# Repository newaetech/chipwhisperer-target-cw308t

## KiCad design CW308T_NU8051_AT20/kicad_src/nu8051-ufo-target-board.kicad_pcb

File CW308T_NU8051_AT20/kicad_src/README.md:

# N76e003 UFO Target board for the Chipwhisper UFO board

Tested and working, gerbers, BOM, and placement files are in `jlcpcb/`

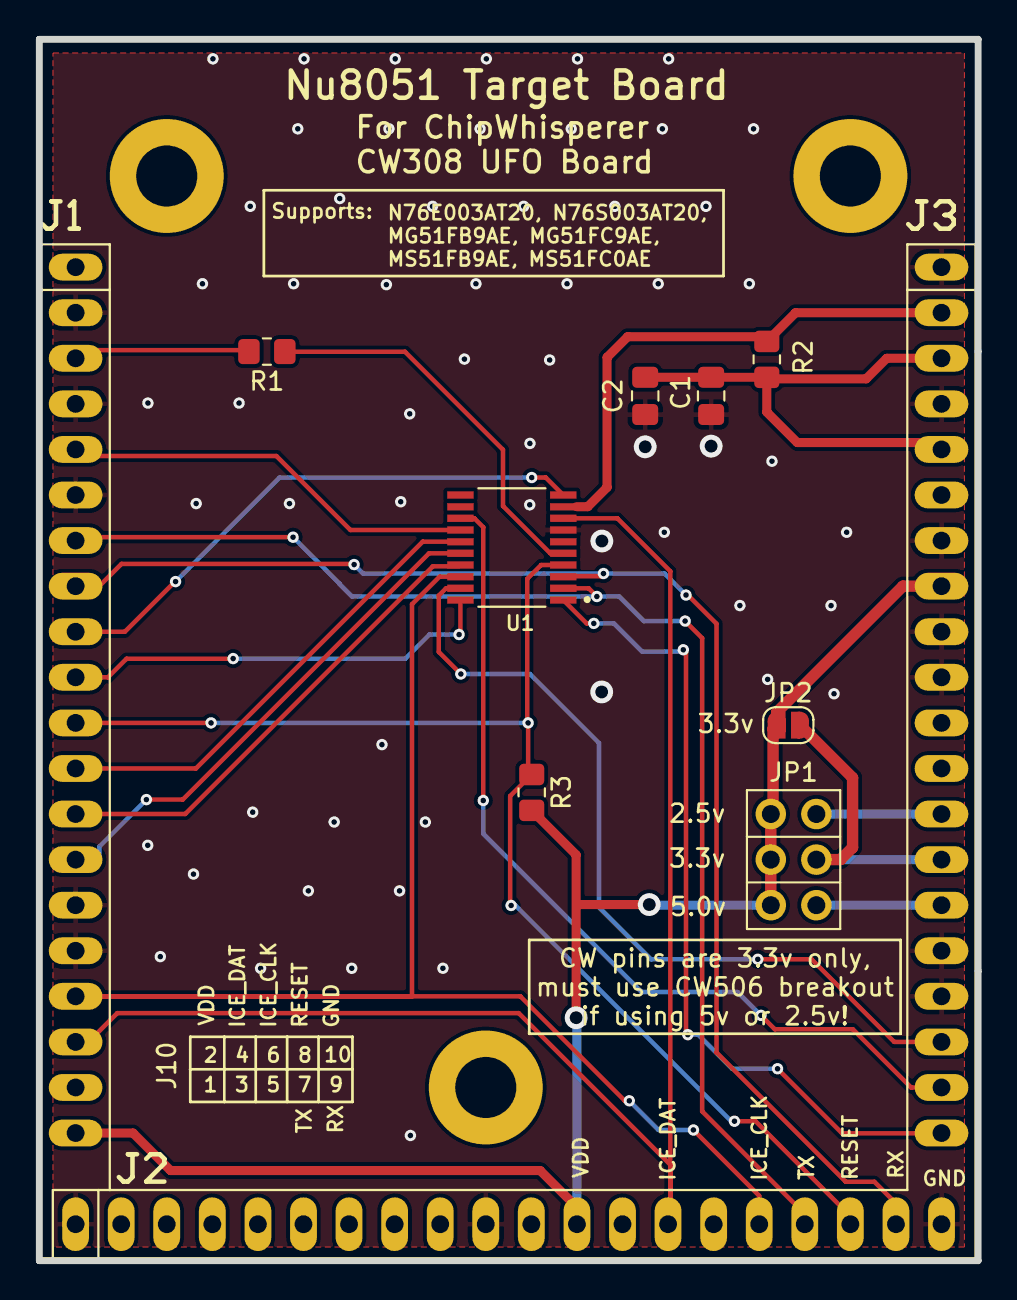
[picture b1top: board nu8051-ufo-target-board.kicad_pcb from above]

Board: 2 copper layers, 52.3 x 68.1 mm, 9 parts (0 on the bottom side), 23 nets.

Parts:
C1: 100nF; C_0805_2012Metric_Pad1.18x1.45mm_HandSolder
C2: 2.2uF (OPT); C_0805_2012Metric_Pad1.18x1.45mm_HandSolder
J1: CW308T_CONNBOARD
JP1: Jumper_2_Open; PinHeader_2x03_P2.54mm_Vertical
JP2: SolderJumper_2_Open; SolderJumper-2_P1.3mm_Open_RoundedPad1.0x1.5mm
R1: 100R; R_0805_2012Metric_Pad1.20x1.40mm_HandSolder
R2: 51R; R_0805_2012Metric_Pad1.20x1.40mm_HandSolder
R3: 10K; R_0805_2012Metric_Pad1.20x1.40mm_HandSolder
U1: N76E003AT20; SOP65P640X120-20N

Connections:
+2V5: J1.C13 (VCC2.5V), JP1.2 (B1)
+3.3V: J1.C14 (VCC3.3V), JP1.4 (B2), JP2.2 (B)
+5V: J1.C15 (VCC5.0V), JP1.6 (B3)
CLK: R1.1, U1.5 (P3.0/~INT0/OSCIN/AIN1)
CLKOUT: J1.A5 (CLKIN), U1.14 (P1.1/PWM1/IC1/AIN7/CLO)
GND: C1.2, C2.2, J1.A2 (GND), J1.A4 (GND), J1.A6 (GND), J1.A15 (GND), J1.A16 (GND), J1.B1 (GND), J1.B10 (GND), J1.B20 (HDR10), J1.C1 (GND), J1.C4 (GND), J1.C7 (GND), J1.C9 (GND), J1.C10 (GND), J1.C16 (GND), J1.C17 (GND), U1.7 (GND)
GPI01: J1.A7 (GPIO1), J1.B17 (HDR7), U1.2 (P0.6/TXD/AIN3)
GPI02: J1.A8 (GPIO2), J1.B19 (HDR9), U1.3 (P0.7/RXD/AIN2)
GPI03: J1.A9 (GPIO3), U1.10 (P1.5/PWM5/IC7/~SS)
GPI04: J1.A10 (GPIO4), U1.20 (P0.4/AIN5/STADC/PWM3/IC3)
LED1: J1.C18 (LED1), U1.19 (P0.3/PWM5/IC5/AIN6)
LED2: J1.C19 (LED2), U1.13 (P1.2/PWM0/IC0)
LED3: J1.C20 (LED3), U1.1 (P0.5/PWM2/IC6/T0/AIN4)
MISO: J1.A13 (MISO), U1.17 (P0.1/PWM4/IC4/MISO)
MOSI: J1.A14 (MOSI), U1.16 (P0.0/PWM3/IC3/MOSI/T1)
unnamed: J1.A3 (CLKOUT), R1.2
unnamed: C1.1, C2.1, J1.C3 (SHUNTH), J1.C5 (FILT_LP), R2.2
PDIC: J1.A17 (PDIC), J1.B16 (HDR6), U1.18 (P0.2/ICPCK/OCDCK/RXD_1/[SCL])
PDID: J1.A18 (PDID), J1.B14 (HDR4), U1.8 (P1.6/[SDA]/TXD_1/ICPDA/OCDDA)
RST: J1.A11 (NRST), J1.B18 (HDR8), R3.2, U1.4 (P2.0/~RST)
SCK: J1.A12 (SCK), U1.15 (P1.0/PWM2/IC2/SPCLK)
VBUS: J1.C2 (SHUNTL), R2.1, U1.9 (VDD)
VCC: J1.A20 (VREF), J1.B12 (HDR2), J1.C8 (FILTIN), JP1.1 (A1), JP1.3 (A2), JP1.5 (A3), JP2.1 (A), R3.1

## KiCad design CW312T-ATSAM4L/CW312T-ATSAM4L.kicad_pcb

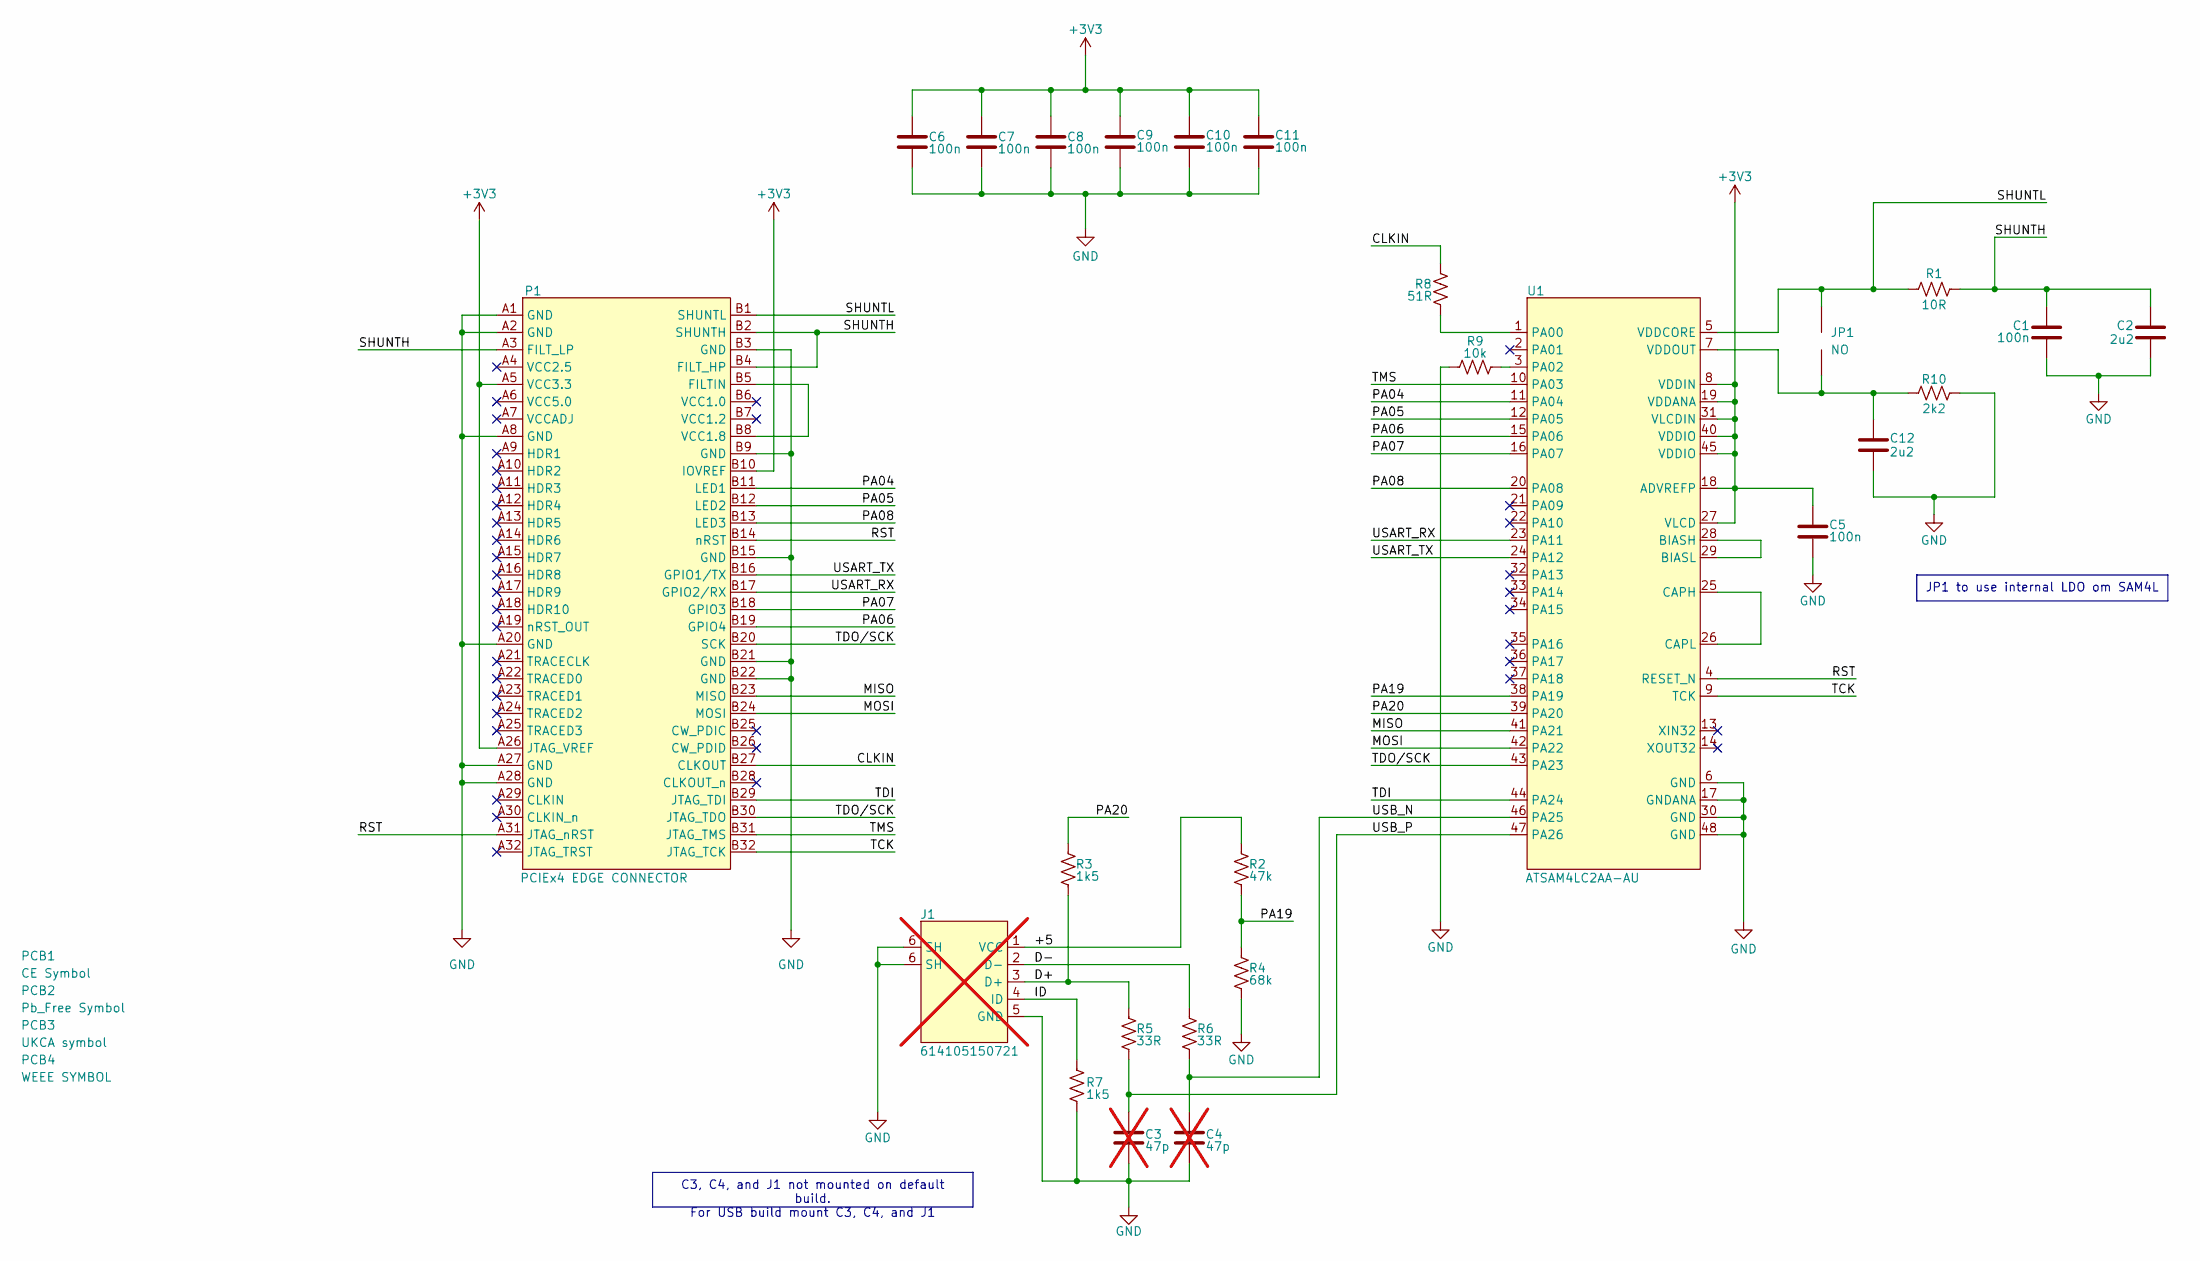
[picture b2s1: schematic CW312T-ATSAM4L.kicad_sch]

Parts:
C1, C5, C6, C7, C8, C9, C10, C11: CAP_100n_10V_0603; C_0603_1608Metric; Manufacturer Part Number CC0603KRX7R6BB104
C2, C12: CAP_2u2_6.3V_0603; C_0603_1608Metric; Manufacturer Part Number CC0603KRX7R5BB225
C3, C4: CAP_47p_50V_0603; C_0603_1608Metric; Manufacturer Part Number CC0603JRNPO9BN470; not fitted
J1: 614105150721; USB_Micro-B_Wuerth_614105150721_Vertical; Manufacturer Part Number 614105150721; not fitted
JP1: SolderJumper-2_P1.3mm_Open_Pad1.0x1.5mm
P1: PCIEx4 EDGE CONNECTOR; CW312_Template
PCB1: CE Symbol; CE-Logo_8.5x6mm_SilkScreen
PCB2: Pb_Free Symbol; Pb_Free_8.0x8.0mm_SilkScreen
PCB3: UKCA symbol; UKCA-Logo_8x8mm_SilkScreen
PCB4: WEEE SYMBOL; WEEE-Logo_5.6x8mm_SilkScreen
R1: RES_10R_0603; R_0603_1608Metric; Manufacturer Part Number RC0603FR-0710RL
R2: RES_47k_0603; R_0603_1608Metric; Manufacturer Part Number RC0603FR-0747KL
R3, R7: RES_1k5_0603; R_0603_1608Metric; Manufacturer Part Number RC0603FR-071K5L
R4: RES_68k_0603; R_0603_1608Metric; Manufacturer Part Number RC0603FR-0768KL
R5, R6: RES_33R_0603; R_0603_1608Metric; Manufacturer Part Number RC0603FR-0733RL
R8: RES_51R_0603; R_0603_1608Metric; Manufacturer Part Number RC0603FR-0751RL
R9: RES_10k_0603; R_0603_1608Metric; Manufacturer Part Number RC0603FR-0710KL
R10: RES_2k2_0603; R_0603_1608Metric; Manufacturer Part Number RC0603FR-072K2L
U1: ATSAM4LC2AA-AU; LQFP-48_7x7mm_P0.5mm; Manufacturer Part Number ATSAM4LC2AA-AU

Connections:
+3V3: C5.2, C6.2, C7.2, C8.2, C9.2, C10.2, C11.2, P1.A5 (VCC3.3), P1.A26 (JTAG_VREF), P1.B10 (IOVREF), U1.8 (VDDIN), U1.18 (ADVREFP), U1.19 (VDDANA), U1.27 (VLCD), U1.31 (VLCDIN), U1.40 (VDDIO), U1.45 (VDDIO)
/+5: J1.1 (VCC), R2.2
/CLKIN: P1.B27 (CLKOUT), R8.2
/D+: J1.3 (D+), R3.1, R5.2
/D-: J1.2 (D-), R6.2
/ID: J1.4 (ID), R7.2
/MISO: P1.B23 (MISO), U1.41 (PA21)
/MOSI: P1.B24 (MOSI), U1.42 (PA22)
/PA04: P1.B11 (LED1), U1.11 (PA04)
/PA05: P1.B12 (LED2), U1.12 (PA05)
/PA06: P1.B19 (GPIO4), U1.15 (PA06)
/PA07: P1.B18 (GPIO3), U1.16 (PA07)
/PA08: P1.B13 (LED3), U1.20 (PA08)
/PA19: R2.1, R4.2, U1.38 (PA19)
/PA20: R3.2, U1.39 (PA20)
/RST: P1.A31 (JTAG_nRST), P1.B14 (nRST), U1.4 (RESET_N)
/SHUNTH: C1.2, C2.1, P1.A3 (FILT_LP), P1.B2 (SHUNTH), P1.B4 (FILT_HP), R1.2
/SHUNTL: JP1.2, P1.B1 (SHUNTL), R1.1, U1.5 (VDDCORE)
/TCK: P1.B32 (JTAG_TCK), U1.9 (TCK)
/TDI: P1.B29 (JTAG_TDI), U1.44 (PA24)
/TDO/SCK: P1.B20 (SCK), P1.B30 (JTAG_TDO), U1.43 (PA23)
/TMS: P1.B31 (JTAG_TMS), U1.10 (PA03)
/USART_RX: P1.B17 (GPIO2/RX), U1.23 (PA11)
/USART_TX: P1.B16 (GPIO1/TX), U1.24 (PA12)
/USB_N: C4.2, R6.1, U1.46 (PA25)
/USB_P: C3.2, R5.1, U1.47 (PA26)
GND: C1.1, C2.2, C3.1, C4.1, C5.1, C6.1, C7.1, C8.1, C9.1, C10.1, C11.1, C12.2, J1.5 (GND), J1.6 (SH), P1.A1 (GND), P1.A2 (GND), P1.A8 (GND), P1.A20 (GND), P1.A27 (GND), P1.A28 (GND), P1.B3 (GND), P1.B9 (GND), P1.B15 (GND), P1.B21 (GND), P1.B22 (GND), R4.1, R7.1, R9.1, R10.2, U1.6 (GND), U1.17 (GNDANA), U1.30 (GND), U1.48 (GND)
unnamed: P1.B5 (FILTIN), P1.B8 (VCC1.8)
unnamed: U1.28 (BIASH), U1.29 (BIASL)
unnamed: U1.25 (CAPH), U1.26 (CAPL)
unnamed: R8.1, U1.1 (PA00)
unnamed: R9.2, U1.3 (PA02)
unnamed: C12.1, JP1.1, R10.1, U1.7 (VDDOUT)

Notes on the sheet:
JP1 to use internal LDO om SAM4L
C3, C4, and J1 not mounted on default build. For USB build mount C3, C4, and J1

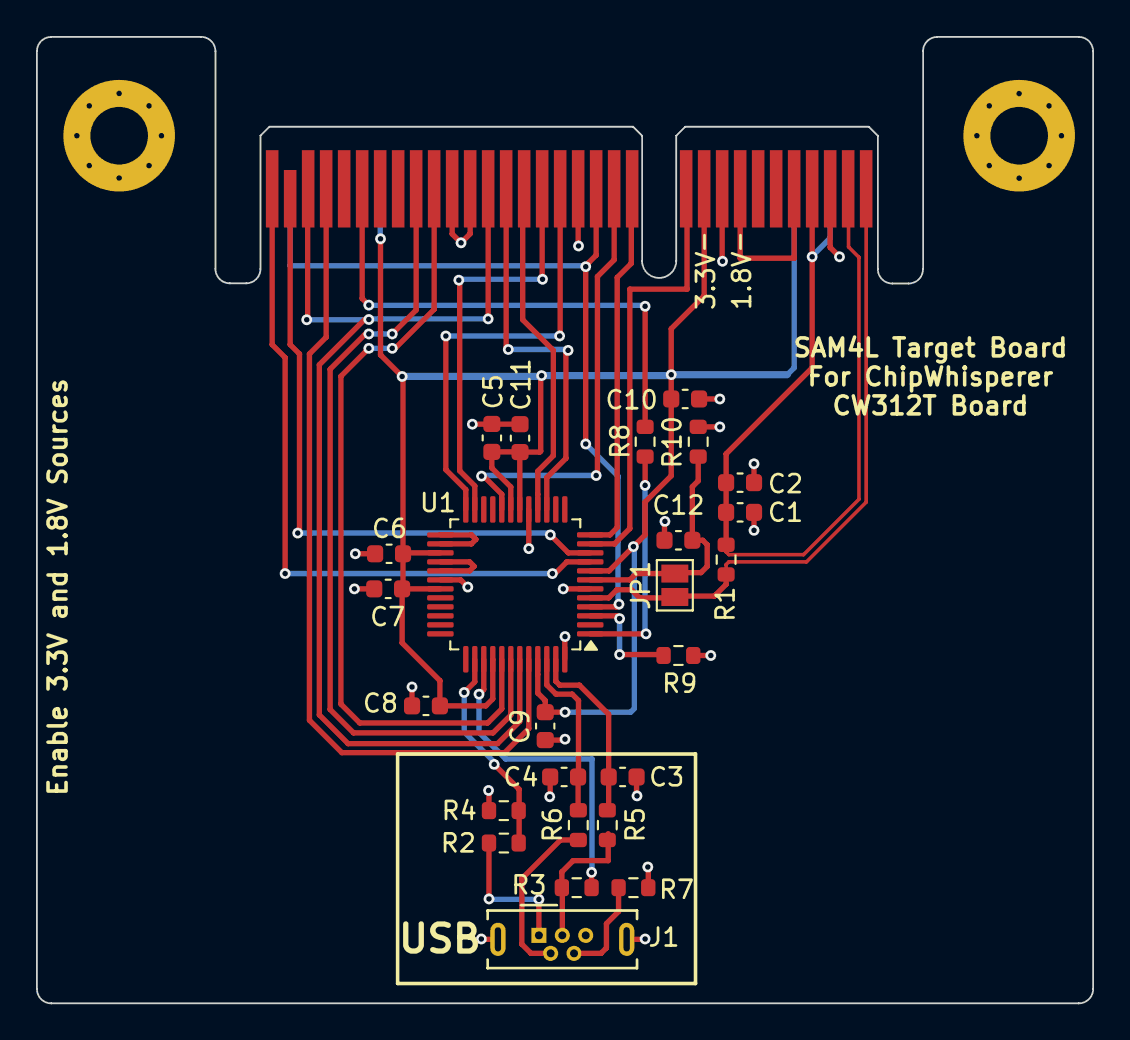
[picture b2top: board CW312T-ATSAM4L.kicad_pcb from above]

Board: 2 copper layers, 58.7 x 53.7 mm, 30 parts (0 on the bottom side), 33 nets.
